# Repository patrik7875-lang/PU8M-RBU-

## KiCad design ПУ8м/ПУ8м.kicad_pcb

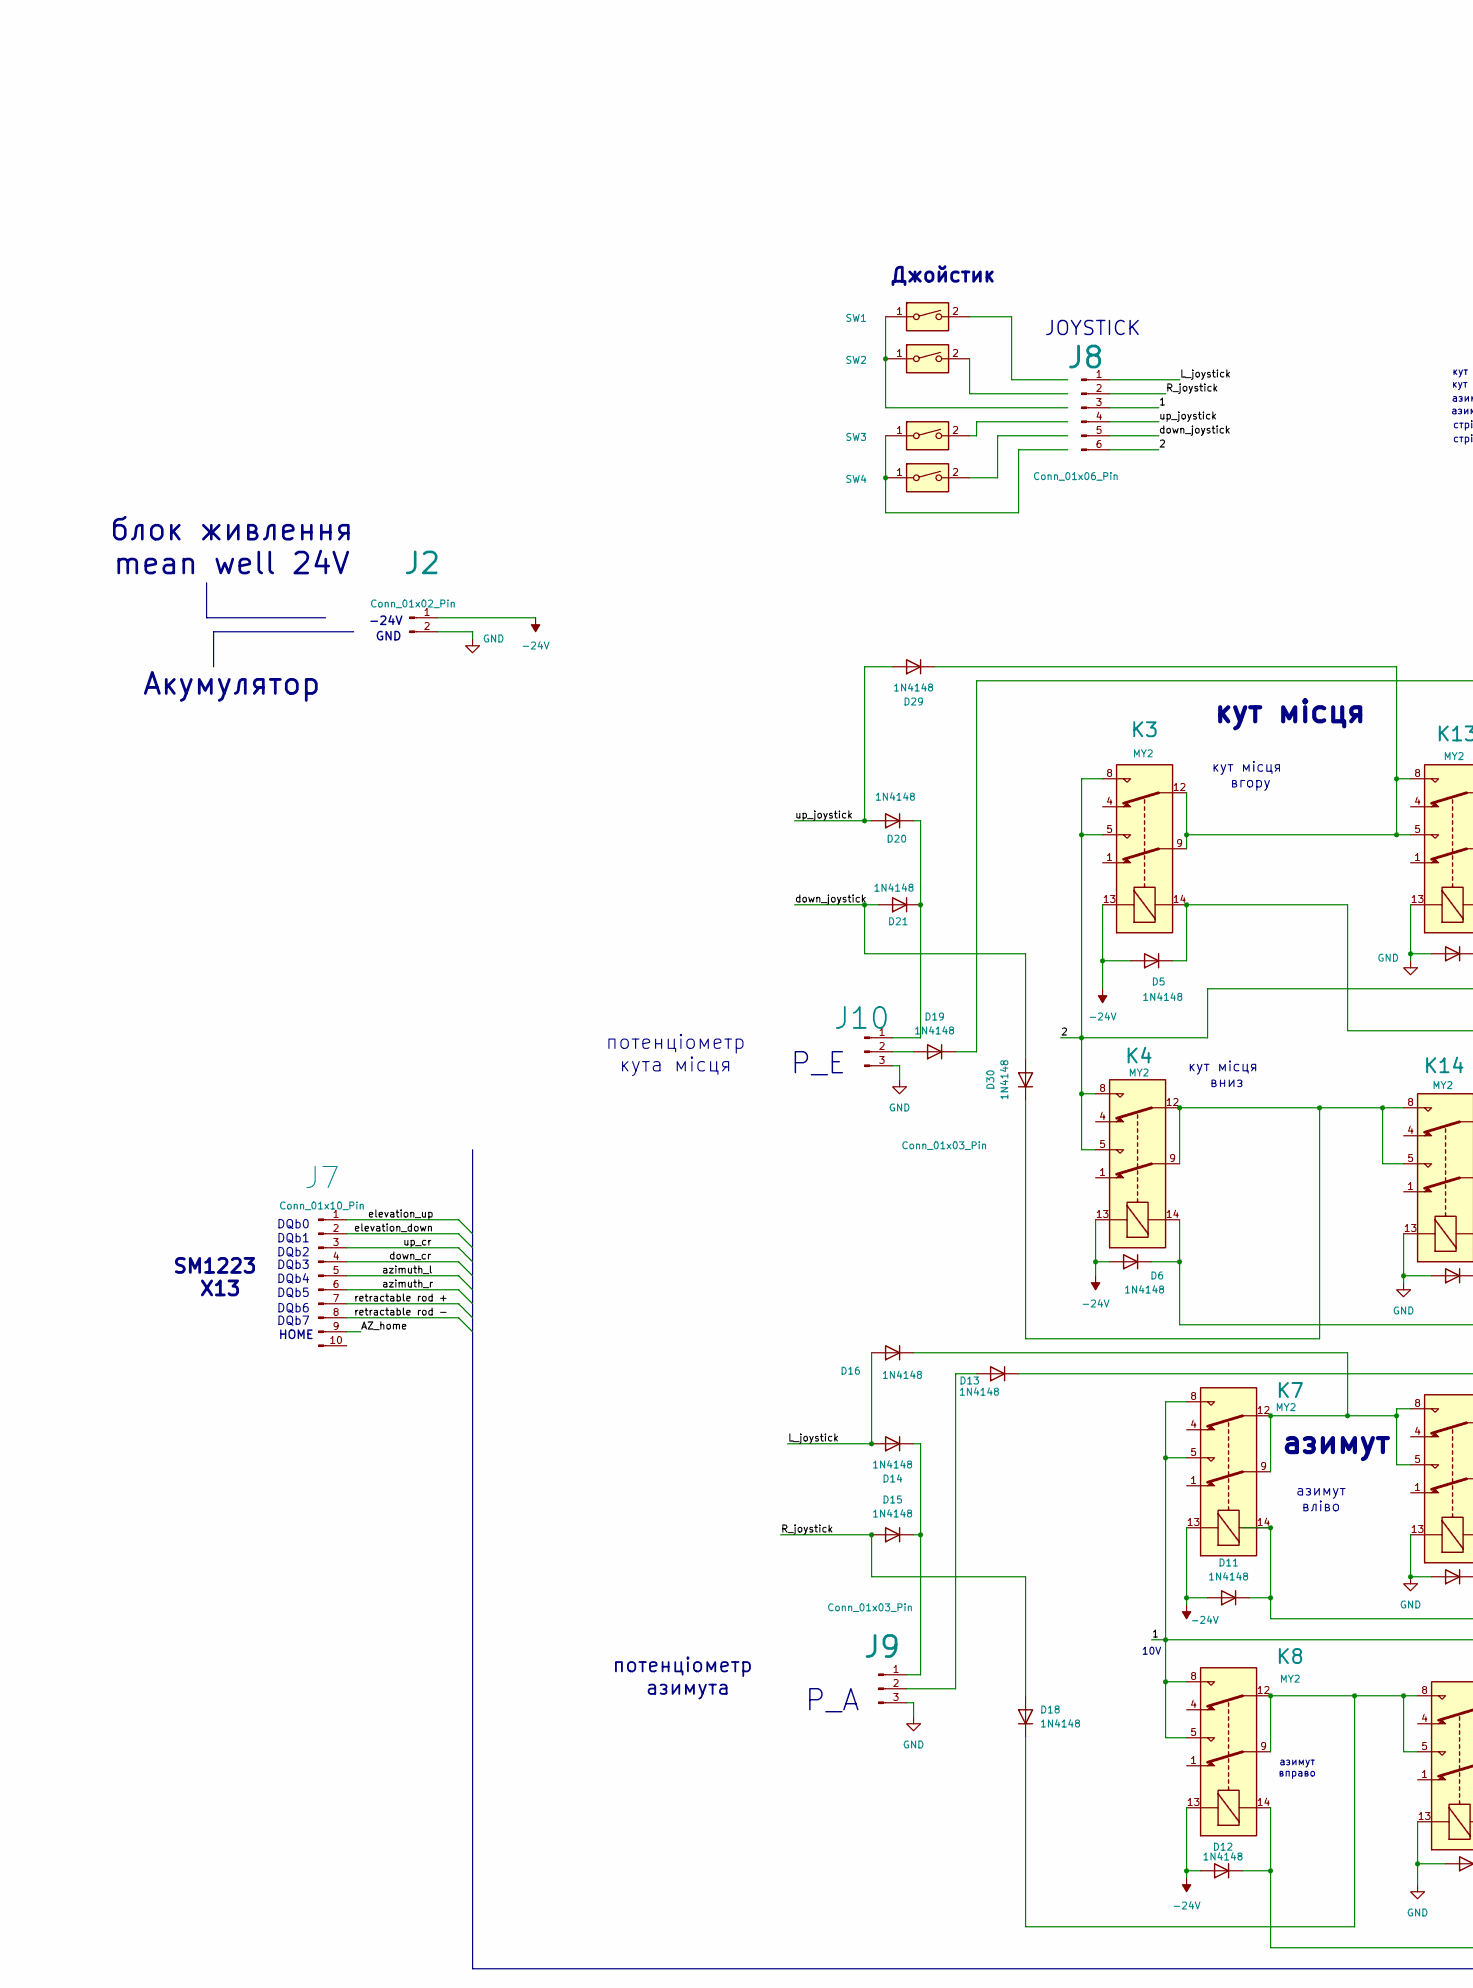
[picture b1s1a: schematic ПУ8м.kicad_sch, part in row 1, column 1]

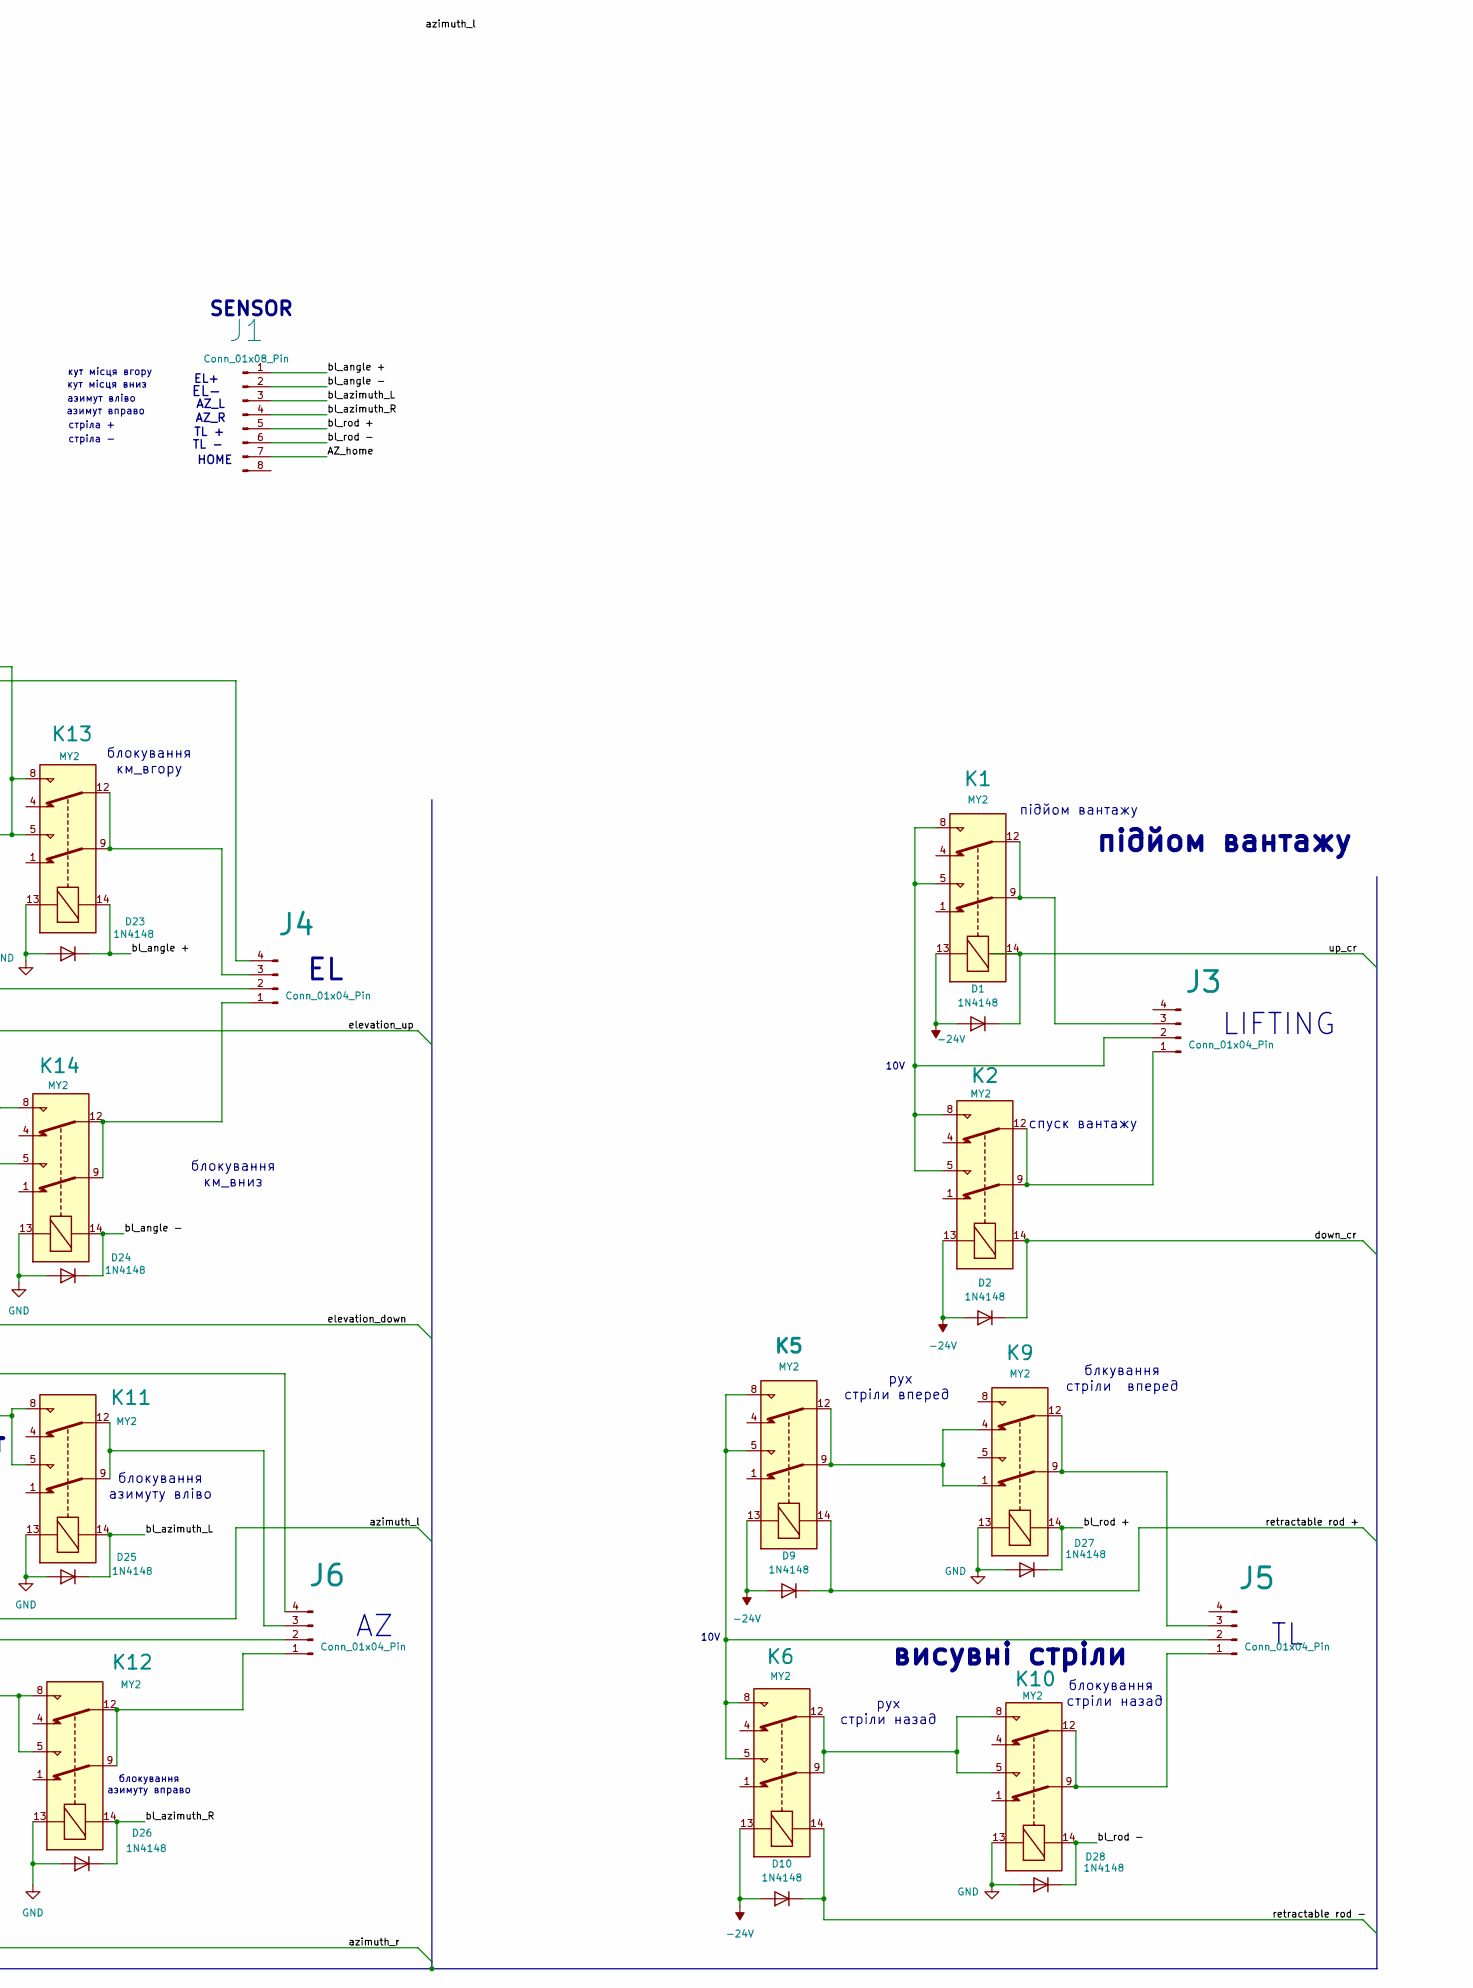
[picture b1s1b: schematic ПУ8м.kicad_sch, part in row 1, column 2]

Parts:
D1, D2, D5, D6, D9, D10, D11, D12, D13, D14, D15, D16, D18, D19, D20, D21, D23, D24, D25, D26, D27, D28, D29, D30: 1N4148; D_SOD-123
J1: Conn_01x08_Pin; TerminalBlock_Phoenix_PT-1,5-8-5.0-H_1x08_P5.00mm_Horizontal
J2: Conn_01x02_Pin; TerminalBlock_Phoenix_PT-1,5-2-5.0-H_1x02_P5.00mm_Horizontal
J3, J4, J5, J6: Conn_01x04_Pin; Molex_KK-254_AE-6410-04A_1x04_P2.54mm_Vertical
J7: Conn_01x10_Pin; TerminalBlock_Phoenix_MKDS-1,5-10_1x10_P5.00mm_Horizontal
J8: Conn_01x06_Pin; Molex_KK-254_AE-6410-06A_1x06_P2.54mm_Vertical
J9, J10: Conn_01x03_Pin; Molex_KK-254_AE-6410-03A_1x03_P2.54mm_Vertical
K1, K2, K3, K4, K5, K6, K7, K8, K9, K10, K11, K12, K13, K14: MY2
SW1, SW2, SW3, SW4: SW_DIP_x01

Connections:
-24V: D1.2 (A), D2.2 (A), D5.2 (A), D6.2 (A), D9.2 (A), D10.2 (A), D11.2 (A), D12.2 (A), J2.1, K1.13, K2.13, K3.13, K4.13, K5.13, K6.13, K7.13, K8.13
/1: J6.2, J8.3, K7.5, K7.8, K8.5, K8.8
/2: J4.2, J8.6, K3.5, K3.8, K4.5, K4.8
/AZ_home: J1.7, J7.9
/L_joystick: D14.2 (A), D16.2 (A), J8.1
/R_joystick: D15.2 (A), D18.2 (A), J8.2
/azimuth_l: D11.1 (K), J7.5, K7.14
/azimuth_r: D12.1 (K), J7.6, K8.14
/bl_angle +: D23.1 (K), J1.1, K13.14
/bl_angle -: D24.1 (K), J1.2, K14.14
/bl_azimuth_L: D25.1 (K), J1.3, K11.14
/bl_azimuth_R: D26.1 (K), J1.4, K12.14
/bl_rod +: D27.1 (K), J1.5, K9.14
/bl_rod -: D28.1 (K), J1.6, K10.14
/down_cr: D2.1 (K), J7.4, K2.14
/down_joystick: D21.2 (A), D30.2 (A), J8.5
/elevation_down: D6.1 (K), J7.2, K4.14
/elevation_up: D5.1 (K), J7.1, K3.14
/retractable rod +: D9.1 (K), J7.7, K5.14
/retractable rod -: D10.1 (K), J7.8, K6.14
/up_cr: D1.1 (K), J7.3, K1.14
/up_joystick: D20.2 (A), D29.2 (A), J8.4
GND: D23.2 (A), D24.2 (A), D25.2 (A), D26.2 (A), D27.2 (A), D28.2 (A), J2.2, J9.3, J10.3, K9.13, K10.13, K11.13, K12.13, K13.13, K14.13
unnamed: D13.2 (A), J9.2
unnamed: D13.1 (K), J6.4
unnamed: D14.1 (K), D15.1 (K), J9.1
unnamed: D16.1 (K), K7.9, K7.12, K11.5, K11.8
unnamed: D18.1 (K), K8.9, K8.12, K12.5, K12.8
unnamed: D19.2 (A), J10.2
unnamed: D19.1 (K), J4.4
unnamed: D20.1 (K), D21.1 (K), J10.1
unnamed: D29.1 (K), K3.9, K3.12, K13.5, K13.8
unnamed: D30.1 (K), K4.9, K4.12, K14.5, K14.8
unnamed: J3.1, K2.9, K2.12
unnamed: J3.2, K1.5, K1.8, K2.5, K2.8
unnamed: J3.3, K1.9, K1.12
unnamed: J4.1, K14.9, K14.12
unnamed: J4.3, K13.9, K13.12
unnamed: J5.1, K10.9, K10.12
unnamed: J5.2, K5.5, K5.8, K6.5, K6.8
unnamed: J5.3, K9.9, K9.12
unnamed: J6.1, K12.9, K12.12
unnamed: J6.3, K11.9, K11.12
unnamed: K5.9, K5.12, K9.1, K9.4
unnamed: K6.9, K6.12, K10.5, K10.8
unnamed: SW1.1, SW2.1
unnamed: SW3.1, SW4.1

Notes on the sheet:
10V
AZ_L
азимут вправо
стріла -
TL -
кут місця вниз
EL+
висувні стріли
SM1223 X13
потенціометр азимута
блокування азимуту вліво
AZ_R
EL-
рух стріли назад
блкування стріли вперед
блокування стріли назад
P_A
стріла +
DQb7
блокування км_вниз
DQb2
DQb4
азимут
Джойстик
блокування км_вгору
блок живлення mean well 24V
-24V
DQb5
кут місця
рух стріли вперед
азимут вліво
підйом вантажу
JOYSTICK
DQb6
Акумулятор
кут місця вгору
кут місця вгору
спуск вантажу
потенціометр кута місця
кут місця вниз

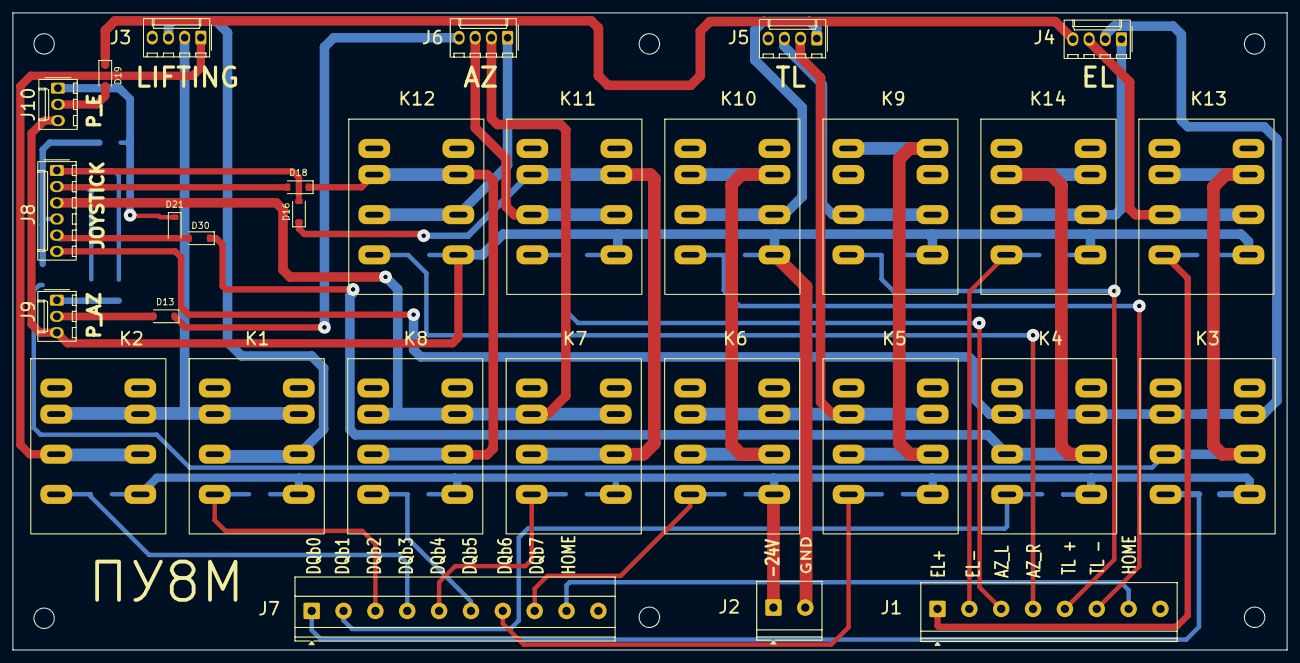
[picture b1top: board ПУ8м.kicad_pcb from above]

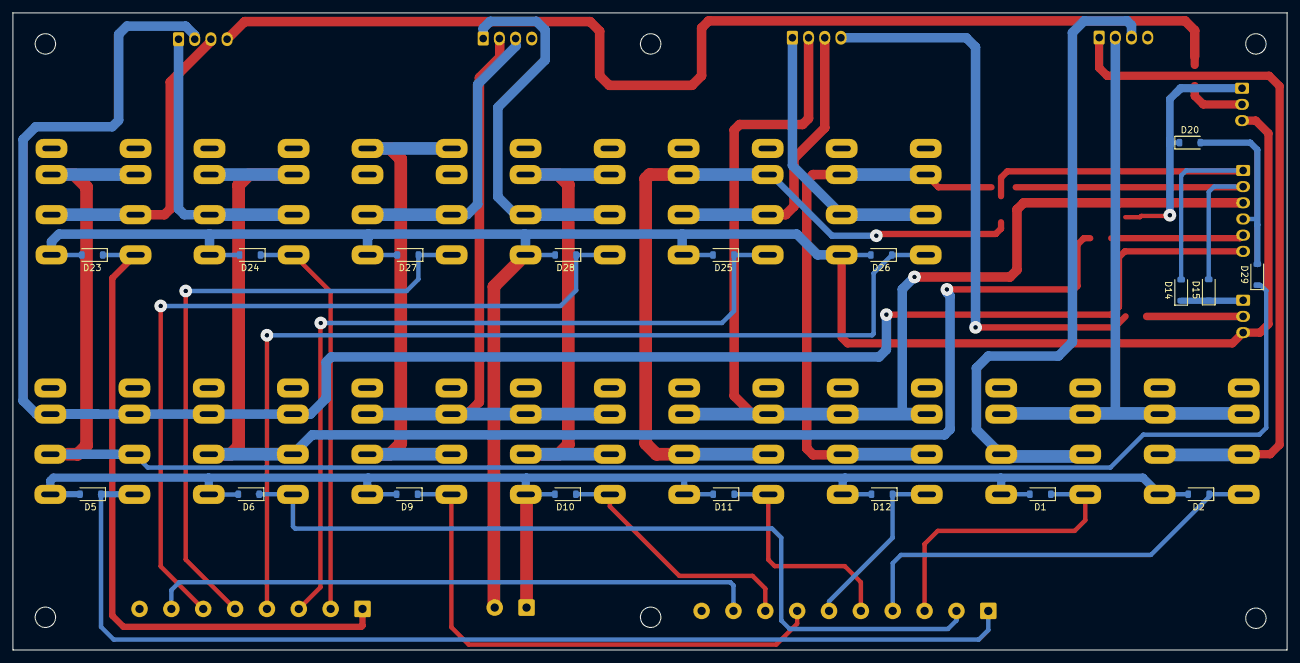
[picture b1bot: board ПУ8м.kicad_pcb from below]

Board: 2 copper layers, 200.0 x 100.0 mm, 48 parts (18 on the bottom side), 45 nets.
